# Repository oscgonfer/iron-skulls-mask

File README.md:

# Iron Skulls Mask - Azul Petróleo

Code and hardware repository for Iron Skulls Azul Petróleo Mask.

## Model

The mask can be 3D printed in two halves ([left](model/Mask_left.stl) and [right](model/Mask_right.stl)) with supports. Use at least 20% infill to avoid problems in the jaw connection. Both halves can be joined with M3 screws with inserts.

## Electronics

There are 45 addressable RGB LEDs (144led/m, skinny type from [Adafruit](https://www.adafruit.com/product/2969)), 2 very high power [white LEDs](https://www.adafruit.com/product/518) (discontinued?) and 1 [laser pointer](https://www.adafruit.com/product/1056). Everything is controlled by a Feather M0 board, with a RFM69 433MHz radio and powered by a 2000mAh LiPo battery. A shield is used to control the different elements. In addition, an [external antenna](https://www.mouser.es/ProductDetail/815-CAC053010-S433) is used for enhanced reach.

- RGB LEDs are powered directly from the battery, controlled with a single pin from the Feather
- The two high power LEDs are controlled via mosfet, in parallel. The LEDs neeed 3.3V, so a high power LDO is necessary
- The laser is controlled via PWM

A bill of materials is found in the [`hardware/controller`](hardware/controller) folder as well as pcb designs for the feather's shield. The kicad files say it's a Atmega 32u4, which can be, but better to use the Atmel SAMD21 (M0) for the extra Flash memory.

### Power

The feather handles battery charge via it's on board charger. The mask is charged via USB.
Since there are so many LEDs, **at least a 0.5C fast discharge rate battery** is necessary if everything is on. This means that the battery will last 2h at this discharge rate, otherwise, at 0.2C (normal rate), it will last 5h:

| Type | Ratio | Max. Current | Duration (theory) |
| -------- | -------- | -------- | -------- |
| Normal     | 0.2C     | 400mA     | 5h |
| Fast     | 0.5C     | 1A     | 2h |

The mask hasn't been tested for full power continuous operation for more than minutes, but it does last >6h in normal operation (not everything on at the same time, all the time).

## Control

The control follows a client-server architecture. Each mask is a server, with an address, and there is a client connected to a computer via USB. The code in both ends is _asynchronous_ so that messages can be sent and arrive to the masks at any time and be responsive.

### Client side

A python script listens to UDP messages and forwards them to a Feather M0 board via USB. This is the [Feather client code](radio/client) (platformio needed). This is the [python script](radio/bridge/bridge.py), using python AsyncIO for serial and OSC/UDP server.

### Server side

A similar code listens on the servers:

- Radiohead is used for receiving packets
- The RGB leds are managed using [NeoPixelBus](https://github.com/Makuna/NeoPixelBus)
- The two high power LEDs and the LED are managed using [JLED](https://github.com/jandelgado/jled)

Animations are static, triggered by a string received via radio, and are stored in [`Animations.h`](radio/server/src/Animations.h). There is a table for describing how the animations are encoded [here](radio/server/src/ANIMATIONS.md).

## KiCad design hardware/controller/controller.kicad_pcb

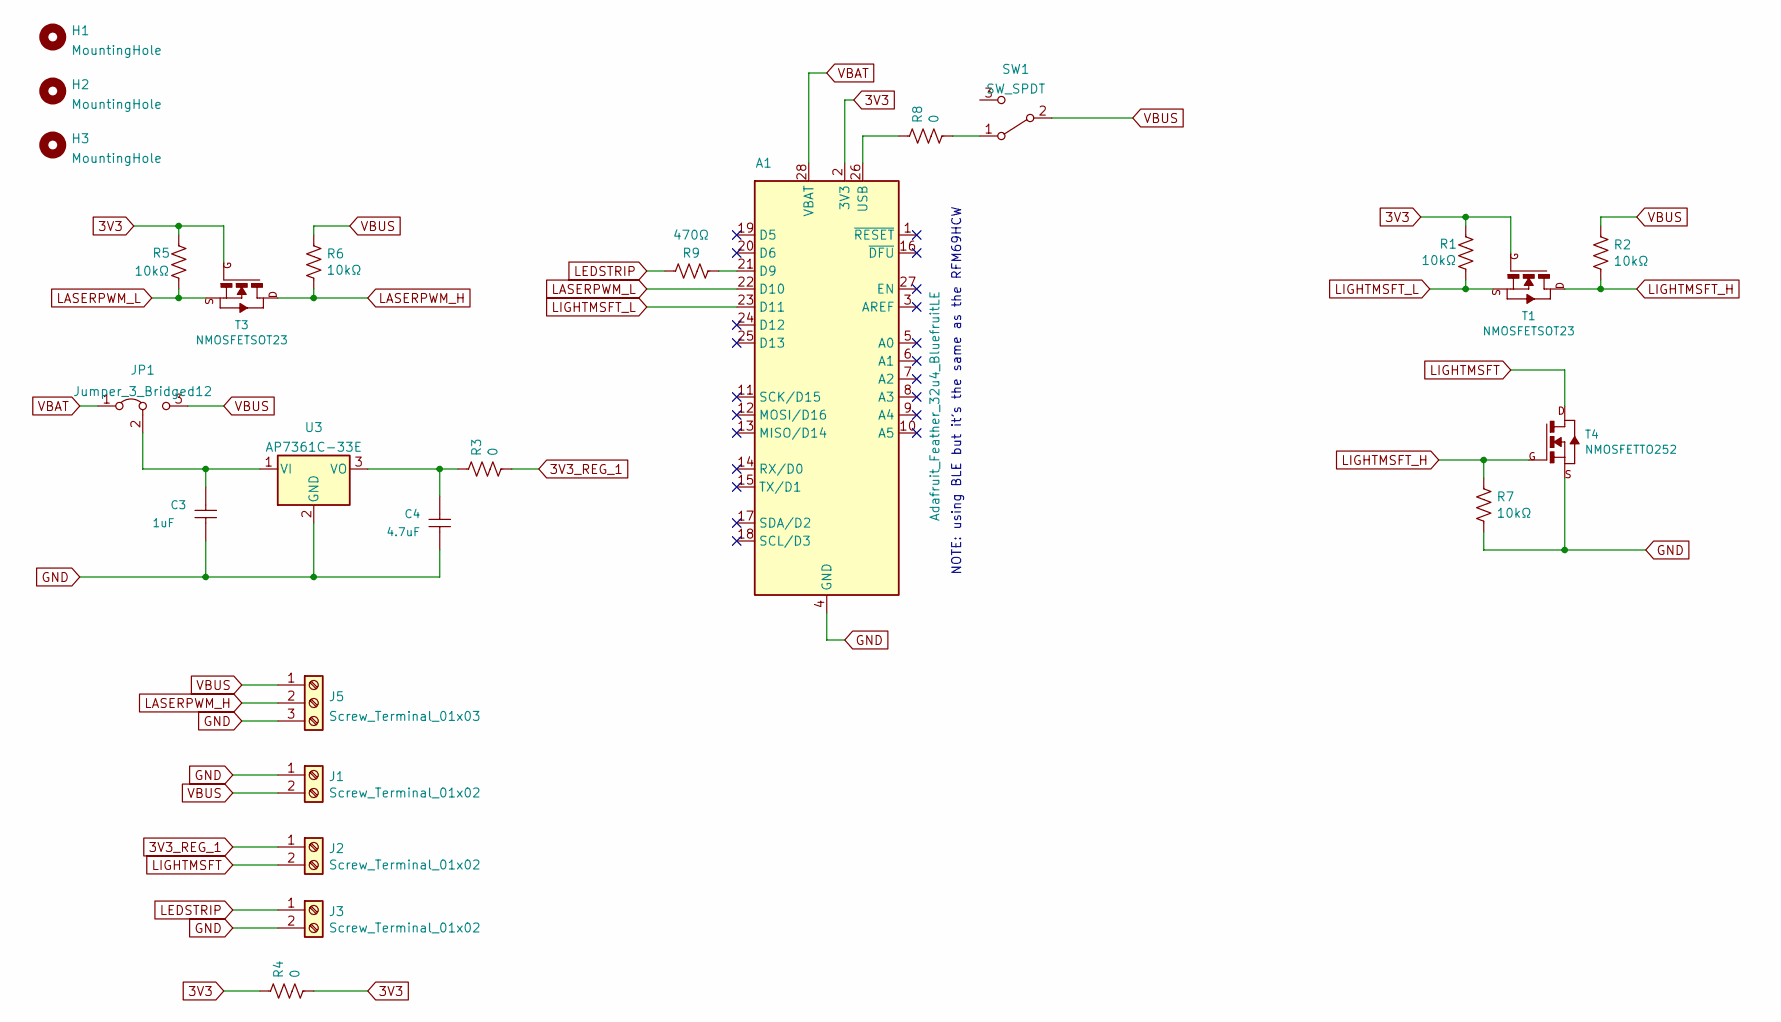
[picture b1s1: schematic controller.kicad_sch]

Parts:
A1: Adafruit_Feather_32u4_BluefruitLE; Adafruit_Feather
C3: 1uF; fab-C1206FAB
C4: 4.7uF; fab-C1206FAB
H1, H2, H3: MountingHole; MountingHole_3.2mm_M3
J1, J2, J3: Screw_Terminal_01x02; TerminalBlock_Phoenix_PT-1,5-2-3.5-H_1x02_P3.50mm_Horizontal
J5: Screw_Terminal_01x03; TerminalBlock_Phoenix_PT-1,5-3-3.5-H_1x03_P3.50mm_Horizontal
JP1: Jumper_3_Bridged12; SolderJumper-3_P1.3mm_Bridged12_RoundedPad1.0x1.5mm_NumberL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
R1, R2, R5, R6, R7: 10kΩ; fab-R1206FAB
R3, R4, R8: 0; fab-R1206FAB
R9: 470Ω; fab-R1206FAB
SW1: SW_SPDT; fab-SPDTSWITCH
T1, T3: NMOSFETSOT23; fab-SOT-23
T4: NMOSFETTO252; fab-TO252
U3: AP7361C-33E; SOT-223-3_TabPin2

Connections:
3V3: A1.2 (3V3), R1.1, R4.1, R4.2, R5.1, T1.3 (G), T3.3 (G)
3V3_REG_1: J2.1, R3.2
GND: A1.4 (GND), C3.2, C4.2, J1.1, J3.2, J5.3, R7.2, T4.2 (S), U3.2 (GND)
LASERPWM_H: J5.2, R6.2, T3.1 (D)
LASERPWM_L: A1.22 (D10), R5.2, T3.2 (S)
LEDSTRIP: J3.1, R9.1
LIGHTMSFT: J2.2, T4.3 (D)
LIGHTMSFT_H: R2.2, R7.1, T1.1 (D), T4.1 (G)
LIGHTMSFT_L: A1.23 (D11), R1.2, T1.2 (S)
unnamed: A1.21 (D9), R9.2
unnamed: A1.26 (USB), R8.1
unnamed: C3.1, JP1.2 (C), U3.1 (VI)
unnamed: C4.1, R3.1, U3.3 (VO)
unnamed: R8.2, SW1.1 (A)
VBAT: A1.28 (VBAT), JP1.1 (A)
VBUS: J1.2, J5.1, JP1.3 (B), R2.1, R6.1, SW1.2 (B)

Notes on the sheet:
NOTE: using BLE but it’s the same as the RFM69HCW

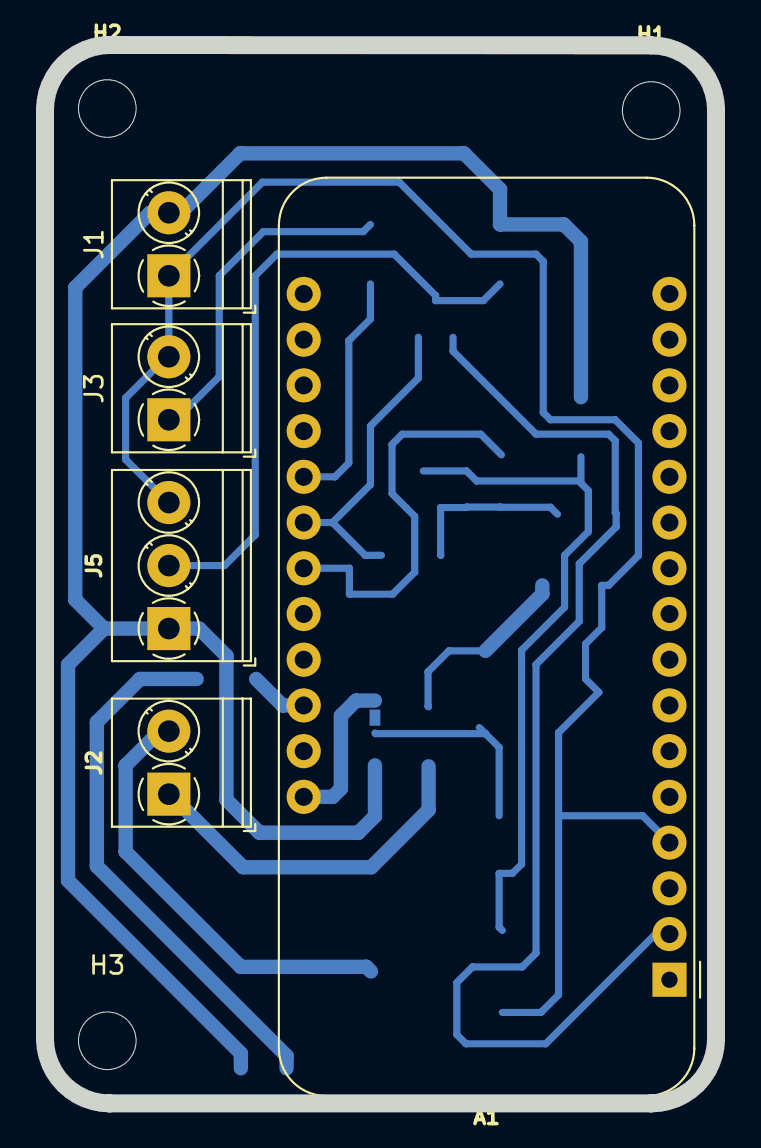
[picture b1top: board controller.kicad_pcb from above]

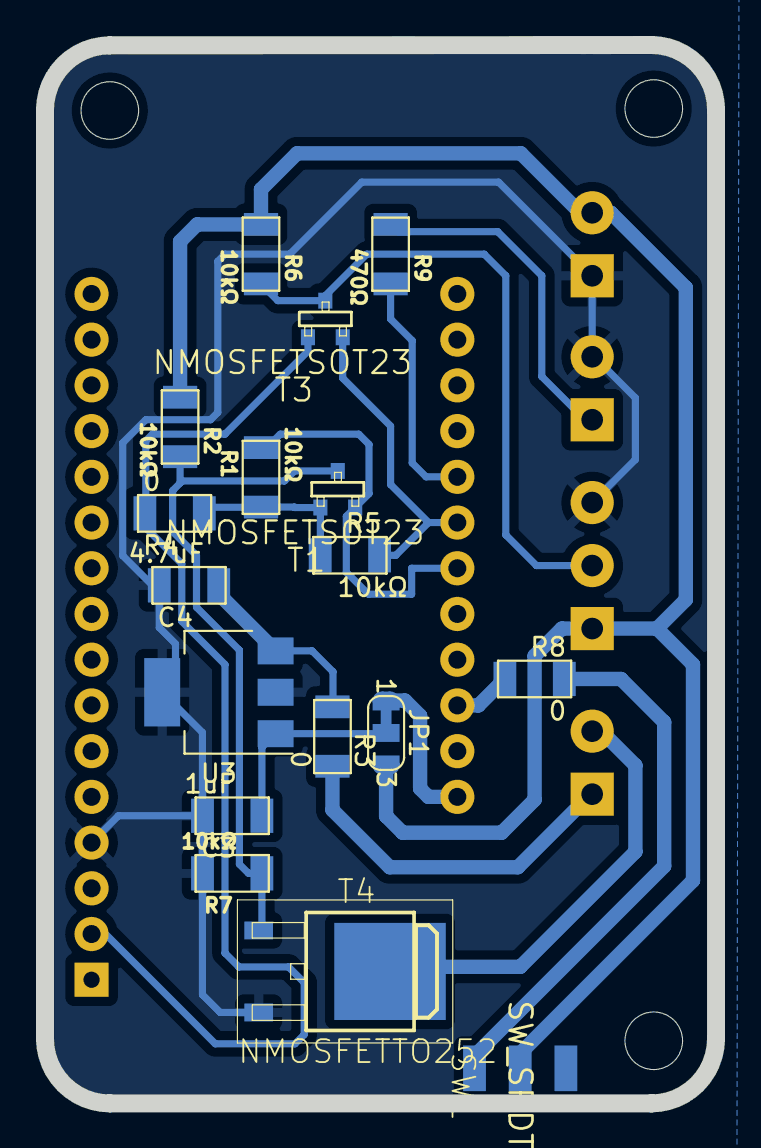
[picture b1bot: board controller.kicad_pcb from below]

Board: 2 copper layers, 37.3 x 58.8 mm, 25 parts (17 on the bottom side), 16 nets.

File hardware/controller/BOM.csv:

SHIELD,,,,,,
,,,,,,
Item,Qty,Reference(s),Value,LibPart,Footprint,Datasheet
1,1,A1,Adafruit_Feather_32u4_BluefruitLE,MCU_Module:Adafruit_Feather_32u4_BluefruitLE,Module:Adafruit_Feather,https://cdn-learn.adafruit.com/downloads/pdf/adafruit-feathe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
2,1,C3,1uF,fab:CAP-UNPOLARIZEDFAB,fab-C1206FAB,
3,1,C4,4.7uF,fab:CAP-UNPOLARIZEDFAB,fab-C1206FAB,
4,3,"H1, H2, H3",MountingHole,Mechanical:MountingHole,MountingHole:MountingHole_3.2mm_M3,~
5,3,"J1, J2, J3",Screw_Terminal_01x02,Connector:Screw_Terminal_01x02,"TerminalBlock_Phoenix:TerminalBlock_Phoenix_PT-1,5-2-3.5-H_1x02_P3.50mm_Horizontal",~
6,1,J5,Screw_Terminal_01x03,Connector:Screw_Terminal_01x03,"TerminalBlock_Phoenix:TerminalBlock_Phoenix_PT-1,5-3-3.5-H_1x03_P3.50mm_Horizontal",~
7,1,JP1,Jumper_3_Bridged12,Jumper:Jumper_3_Bridged12,Jumper:SolderJumper-3_P1.3mm_Bridged12_RoundedPad1.0x1.5mm_NumberLabels,~
8,5,"R1, R2, R5, R6, R7",10kΩ,Device:R_US,fab:fab-R1206FAB,~
9,3,"R3, R4, R8",0,Device:R_US,fab:fab-R1206FAB,~
10,1,R9,470Ω,Device:R_US,fab:fab-R1206FAB,~
11,1,SW1,SW_SPDT,Switch:SW_SPDT,fab:fab-SPDTSWITCH,~
12,2,"T1, T3",NMOSFETSOT23,fab:NMOSFETSOT23,fab-SOT-23,
13,1,T4,NMOSFETTO252,fab:NMOSFETTO252,fab-TO252,
14,1,U3,AP7361C-33E,Regulator_Linear:AP7361C-33E,Package_TO_SOT_SMD:SOT-223-3_TabPin2,https://www.diodes.com/assets/Datasheets/AP7361C.pdf
,,,,,,
LIGHTS,,,,,,
,,,,,,
Item,Qty,Description,Manufacturer and PN,Mouser Link,,
1,1,Laser pointer,TTL Laser Diode - 5mW 650nm Red - 50KHz Max,https://www.adafruit.com/product/1056,,
1,2,High power White LEDs,1 Watt Cool White LED - Heatsink Mounted,https://www.adafruit.com/product/518,,
1,1,NeoPixel 144led/m skinny,Adafruit Mini Skinny NeoPixel Digital RGB LED Strip - 144 LED/m - 1m WHITE,https://www.adafruit.com/product/2969,,
,,,,,,
EXTRAS,,,,,,
,,,,,,
Item,Qty,Description,Manufacturer and PN,Mouser Link,,
1,1,433MHz Antenna,Abracon AEACAC053010-S433 ,https://eu.mouser.com/ProductDetail/815-CAC053010-S433,,

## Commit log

2022-01-09 Add gitignore
2022-01-09 Initial commit with radio basic example
2022-01-09 Fix typo
2022-01-09 Updated code to support feather32u4
2022-01-16 Add first schematic for pcb
2022-01-23 Add bridge script from UDP server to client and adapt client script
2022-01-23 Minor fix
2022-01-30 Add checksum to message
2022-02-06 Add overkill controller version
2022-02-13 Last version of controller
2022-02-13 Move to radiohead mesh
2022-02-13 Add repeater node
2022-02-13 WIP Move to NeoPixelBus
2022-02-21 Move to NeoPixelBus and consolidate animations
2022-02-22 Add face parts to animations
2022-02-22 Add timestamp to bridge
2022-02-22 Make bridge for udp to enttec
2022-02-22 Add test UDP-OSC debugging tool
2022-02-23 Modify enttec.py for OSC only on current levels
2022-03-04 electronics with separate power sources and switch
2022-03-15 Bridge eos light for sound2light patching
2022-03-15 Add names to bridge and patch
2022-03-15 Move channels to aux patch
2022-03-15 Lava version with reduced leds
2022-03-15 Improve enttec bridge
2022-03-16 Fix update after laser fade slow
2022-03-16 Add different states to eos bridge
2022-03-16 Remove feather32u4 environment
2022-03-28 Added mask models
2022-04-05 Fix python additional eos and udp scripts
2022-04-05 Remove exports
2022-08-28 Add demo script
2022-08-28 Fix NeoPixelBus version
2023-01-02 Improve documentation for the mask
